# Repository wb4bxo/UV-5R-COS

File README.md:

# UV-5R-COS
I have put together a little circuit that allows connection to a Baofeng UV-5R HT providing COS without having to open and modify the radio itself. This works great for AllStar, packet, APRS, or most anything that requires a soundcard connection to the radio complete with COS. I have even used this circuit without the sound card to connect to an RC-210 repeater controller.
 
I built the circuit based on the schematic of the UV-5R but I believe most of the Chinese radios will work with it. I have tried it on several different Chinese radios including the Anytone AT-D868UV DMR radio and they all worked fine. However, even though these radios are mimicking the Kenwood two prong speaker/mic connector, this circuit will not work on my Kenwood TH-F6. This is due to the fact that the Chinese radios do not block the DC of the audio amp from reaching the headset, which is why you hear a pop when the squelch opens and closes on these radios, and is what this circuit counts on to turn on Q1 and provide COS. The Kenwood doesn’t work (or have the pop) because it has a blocking capacitor and an MOS switch in the audio line that prevents the DC from coming out the jack. But I’m much happier using a $35 radio for this purpose anyway.
 
I’ve hand etched a couple of boards for it so far and may send it to a board house to make some prettier boards, especially if others are interested in it (I’ve already quoted them and its just too pricey for small quantities, which is why I decided to hand make the few I needed). The boards I have made have some extra pads on the end to allow soldering directly to the audio jacks of one of the EBay sound FOBs, just makes it a bit cleaner than having to cable that side of it, though it still requires the two jumpers to the GPIO lines on the sound chip. Also note that there is an extra connection at Pin 4 on the sound card side that should allow using with an RA-35 or similar that already has the open collector driver for PTT. I have not tried this on an RA-35 but feel confident it would work, my target was primarily the CM108 open board sound FOB you can get on EBay and Amazon.
https://www.ebay.com/itm/CM108-USB-Drive-Free-Sound-Card-Laptop-Computer-External-Sound-Card-Module-New/263928310585?hash=item3d735a6b39:g:SSwAAOSwEVlcDcAU:rk:1:pf:0
 
Also note there is no activity detection nor time out timer in this circuit, so I leave the TOT of the attached radio set to something appropriate in case things get hung up in transmit. And as with other interfaces, make sure to keep the RF from the attached HT from getting back into the RPi.

Here is a link to some pictures and such as it progressed. The folder of this version is PCB-02.
https://www.dropbox.com/scl/fo/ijx6qdvklskfgv19kaams/ABsIuqHEEbqoYNm4X1Uc1b4?rlkey=346zcdpkfad4y5mk4jwmj165i&dl=0

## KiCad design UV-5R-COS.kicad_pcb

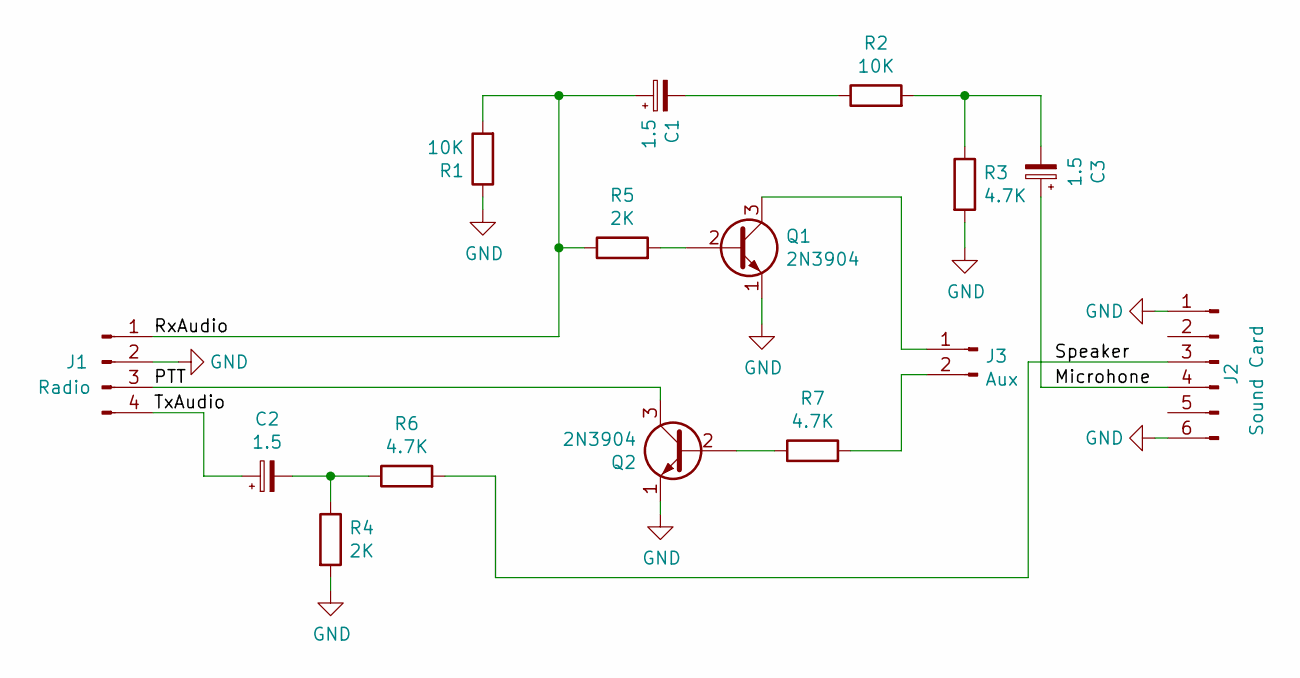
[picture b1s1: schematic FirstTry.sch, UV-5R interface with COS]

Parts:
C1, C2, C3: 1.5; CP_Radial_D4.0mm_P2.00mm
J1: Radio; PinHeader_1x04_P2.54mm_Vertical
J2: Sound Card; AUDIO JACKS
J3: Aux; PinHeader_2x01_P2.54mm_Vertical
Q1, Q2: 2N3904; TO-92_Inline
R1, R2: 10K; R_Axial_DIN0207_L6.3mm_D2.5mm_P2.54mm_Vertical
R3, R6, R7: 4.7K; R_Axial_DIN0207_L6.3mm_D2.5mm_P2.54mm_Vertical
R4, R5: 2K; R_Axial_DIN0207_L6.3mm_D2.5mm_P2.54mm_Vertical

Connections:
GND: J1.2, J2.1, J2.6, Q1.1 (E), Q2.1 (E), R1.1, R3.2, R4.2
unnamed: C1.1, J1.1, R1.2, R5.1
unnamed: C1.2, R2.1
unnamed: C2.1, J1.4
unnamed: C2.2, R4.1, R6.1
unnamed: C3.1, J2.4
unnamed: C3.2, R2.2, R3.1
unnamed: J1.3, Q2.3 (C)
unnamed: J2.3, R6.2
unnamed: J3.1, Q1.3 (C)
unnamed: J3.2, R7.2
unnamed: Q1.2 (B), R5.2
unnamed: Q2.2 (B), R7.1

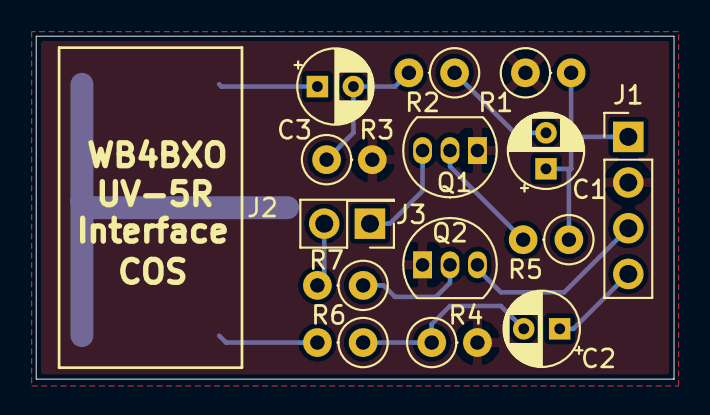
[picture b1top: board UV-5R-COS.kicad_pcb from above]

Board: 2 copper layers, 35.4 x 19.0 mm, 15 parts (0 on the bottom side), 13 nets.

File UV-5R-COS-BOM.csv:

"Id";"Designator";"Package";"Quantity";"Designation";"Supplier and ref";
1;"J1";"PinHeader_1x04_P2.54mm_Vertical";1;"Radio";;;
2;"C1,C2,C3";"CP_Radial_D4.0mm_P2.00mm";3;"1.5";;;
3;"J3";"PinHeader_2x01_P2.54mm_Vertical";1;"Aux";;;
4;"J2";"AUDIO JACKS";1;"Sound Card";;;
5;"R5,R4";"R_Axial_DIN0207_L6.3mm_D2.5mm_P2.54mm_Vertical";2;"2K";;;
6;"Q2,Q1";"TO-92_Inline";2;"2N3904";;;
7;"R1,R2";"R_Axial_DIN0207_L6.3mm_D2.5mm_P2.54mm_Vertical";2;"10K";;;
8;"R7,R3,R6";"R_Axial_DIN0207_L6.3mm_D2.5mm_P2.54mm_Vertical";3;"4.7K";;;

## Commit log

2022-12-02 Original
    As built 20190331

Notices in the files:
UV-5R-COS.kicad_pcb:
License CC by 4.0
